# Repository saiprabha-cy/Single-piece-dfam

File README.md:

# Single-Piece DfAM Redesign of a Liquid Rocket Injector/Nozzle Assembly

A capstone project applying **Design for Additive Manufacturing (DfAM)**
principles to a small liquid rocket engine injector/nozzle assembly —
exploring how a traditionally multi-part, bolted engine assembly can be
redesigned as a single consolidated 3D-printed part.

## Motivation

Several modern small-launch-vehicle companies have moved toward 3D-printing
entire rocket engines as a single piece, eliminating the joints, fasteners,
and assembly steps of traditionally machined multi-part engines. This
project applies that same design philosophy at a smaller, student-accessible
scale: take a conventionally-designed multi-part injector/nozzle assembly,
redesign it as one consolidated additively-manufactured part, and validate
the redesign with both hand calculations and simulation.

## Project Stages

| Stage | Folder | Status |
|---|---|---|
| 1. Propulsion calculations | `01_calculations/` | ✅ Complete |
| 2. Baseline multi-part CAD | `02_cad/baseline_multipart/` | ✅ Complete |
| 3. Single-piece DfAM redesign | `02_cad/dfam_redesign/` | ✅ Complete |
| 4. Structural/thermal validation | `03_simulation/` | ✅ Structural complete; thermal documented as a known limitation |
| 5. Sensor/telemetry board | `04_kicad_board/` | ✅ Complete (0 DRC errors) |
| 6. Print-readiness analysis | `05_print_readiness/` | 🔜 Scoped as future work (see below) |
| 7. Final report | `06_report/` | ✅ Complete |

## Design Case (Assumed, Representative Values)

This project uses **representative values** for a generic small LOX/Kerosene
test-case engine, not any specific company's proprietary specifications.

- Target thrust: 3,000 N
- Chamber pressure: 20 bar
- Propellants: LOX / Kerosene (RP-1)
- Assumed sea-level Isp: 290 s

## Key Results

| Metric | Baseline (multi-part) | Redesign (single-piece) |
|---|---|---|
| Part count | 3 | 1 |
| Fastener interfaces | 2 (1 bolted, 1 rigid-joint only) | 0 |
| Mounting holes | 8 | 0 |
| Cooling provisions | None | 6 integrated channels |
| Structural safety factor (20 bar) | — | 6.24 (Ti-6Al-4V, SimScale) |

## Tools Used

- **Python** (SciPy) — propulsion calculations
- **Autodesk Fusion 360** (Personal Use license) — CAD modeling + built-in simulation
- **SimScale** — structural/thermal validation
- **KiCad** — sensor/telemetry PCB design

### Future Extensions
- **PrusaSlicer / Cura** — print-readiness and support-structure analysis
  (scoped as future work; see `05_print_readiness/`)
- Coolant inlet/outlet port routing on the DfAM redesign
- Full channel count (6 → 24) for production-representative coverage
- Chamber L* correction (increase straight-section length for realistic
  combustion residence time)

## Known Limitations

- **Chamber L\*** (characteristic length) is 263mm against a typical
  800-1500mm range for LOX/Kerosene engines — the as-modeled chamber is
  shorter than standard practice would recommend. This is a known,
  documented simplification; it does not affect the validity of the
  single-piece consolidation comparison, which is geometry-independent of
  chamber length. See `01_calculations/results/design_targets.json`.
- **Thermal simulation** was attempted in SimScale but diverged (likely due
  to an incomplete fluid-flow boundary definition in the initial CHT setup).
  Due to free-tier compute limits, a corrected re-run was not completed.
  The Stage 1 hand-calculated estimate (19.2 MW/m², target wall temp 800K)
  is retained as the primary thermal reference. See
  `03_simulation/validation_comparison.md`.
- **Cooling channel count** was reduced from a production-representative
  24 channels to 6, to keep the modeling scope achievable within the
  project timeline.
- **Print-readiness analysis** (slicer-based orientation/support check) was
  not completed; see Future Extensions above.

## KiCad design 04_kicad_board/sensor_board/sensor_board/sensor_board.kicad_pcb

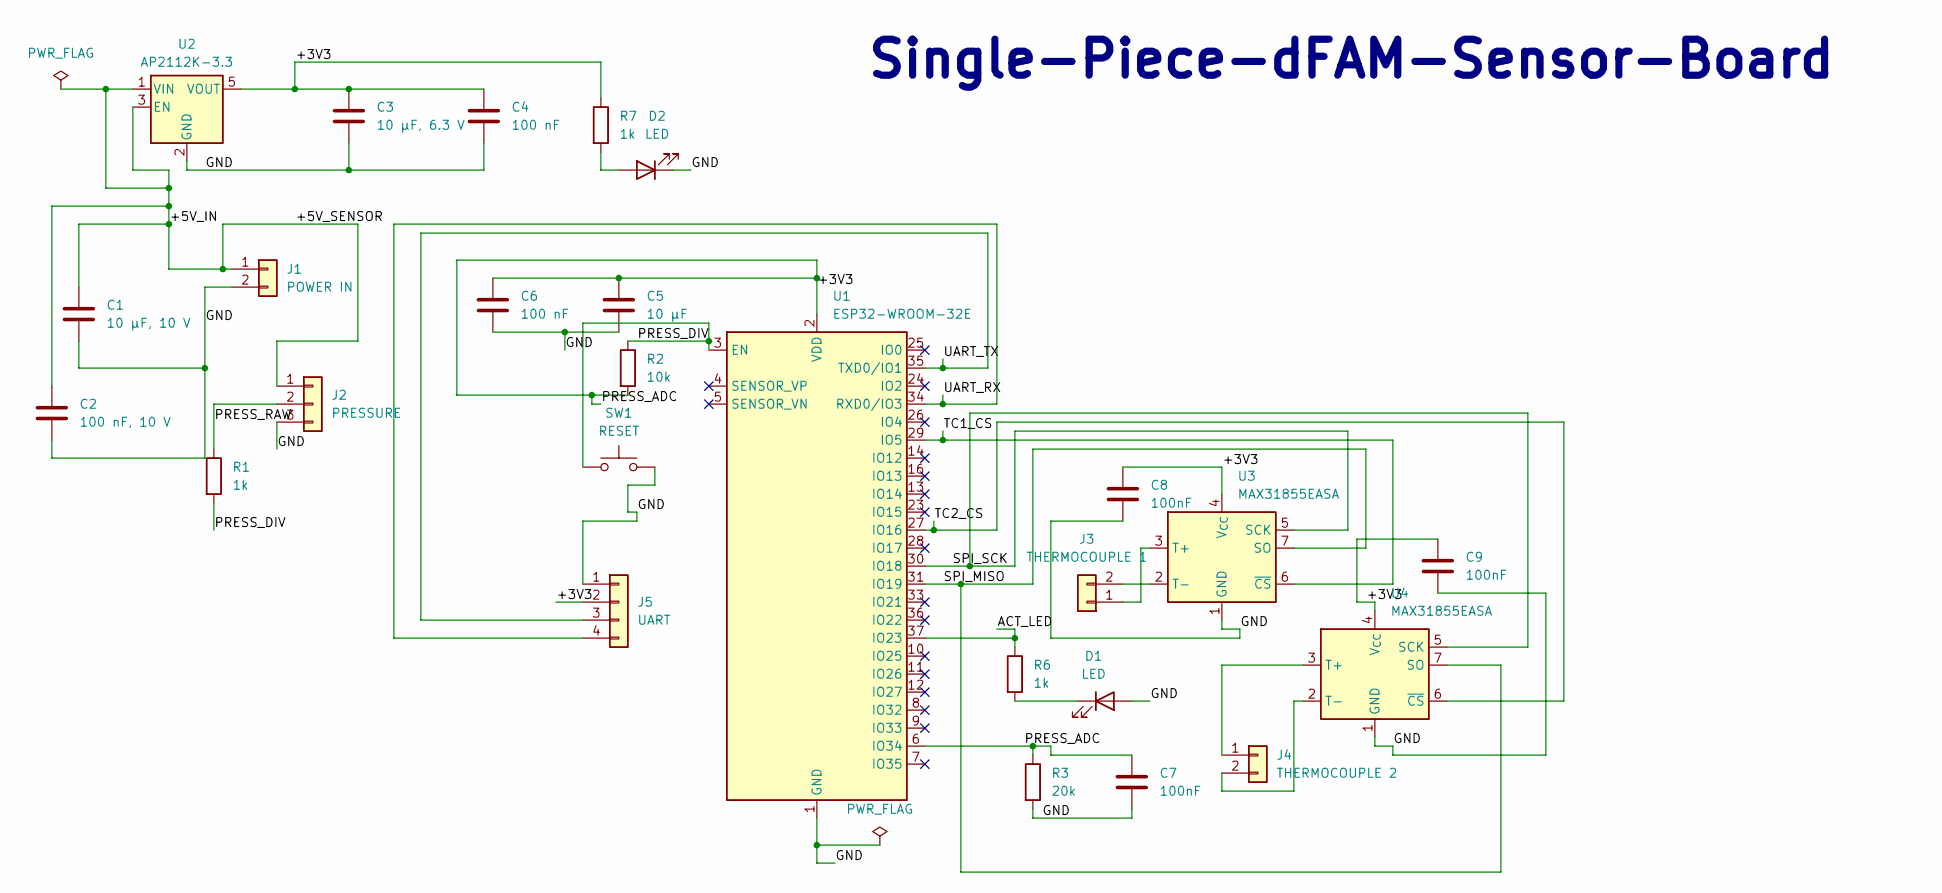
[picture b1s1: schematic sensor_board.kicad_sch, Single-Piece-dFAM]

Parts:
C1: 10 µF, 10 V; C_0805_2012Metric
C2: 100 nF, 10 V; C_0603_1608Metric
C3: 10 µF, 6.3 V; C_0805_2012Metric
C4, C6: 100 nF; C_0603_1608Metric
C5: 10 µF; C_0805_2012Metric
C7, C8, C9: 100nF; C_0603_1608Metric
D1, D2: LED; LED_0603_1608Metric
J1: POWER IN; PhoenixContact_MSTBA_2,5_2-G_1x02_P5.00mm_Horizontal
J2: PRESSURE; PinHeader_1x03_P2.54mm_Vertical
J3: THERMOCOUPLE 1; PinHeader_1x02_P2.54mm_Vertical
J4: THERMOCOUPLE 2; PinHeader_1x02_P2.54mm_Vertical
J5: UART; PinHeader_1x04_P2.54mm_Vertical
R1, R6, R7: 1k; R_0603_1608Metric
R2: 10k; R_0603_1608Metric
R3: 20k; R_0603_1608Metric
SW1: RESET; SW_SPST_TL3305A
U1: ESP32-WROOM-32E; ESP32-WROOM-32
U2: AP2112K-3.3; SOT-23-5
U3, U4: MAX31855EASA; SOIC-8_3.9x4.9mm_P1.27mm

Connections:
/+3V3: C3.1, C4.1, C5.1, C6.1, C7.1, C8.1, C9.1, J5.2, R2.2, R3.1, R7.1, U1.2 (VDD), U1.6 (IO34), U2.5 (VOUT), U3.4 (V_{CC}), U4.4 (V_{CC})
/+5V_IN: C1.1, C2.1, J1.1, J2.1, U2.1 (VIN), U2.3 (EN)
/ACT_LED: R6.1, U1.37 (IO23)
/GND: C1.2, C2.2, C3.2, C4.2, C5.2, C6.2, C7.2, C8.2, C9.2, D1.2 (A), D2.1 (K), J1.2, J2.3, J5.1, R3.2, SW1.2, U1.1 (GND), U1.15 (GND), U1.38 (GND), U1.39 (GND), U2.2 (GND), U3.1 (GND), U4.1 (GND)
/PRESS_DIV: R1.2, R2.1, SW1.1, U1.3 (EN)
/PRESS_RAW: J2.2, R1.1
/SPI_MISO: U1.31 (IO19), U3.7 (SO), U4.7 (SO)
/SPI_SCK: U1.30 (IO18), U3.5 (SCK), U4.5 (SCK)
/TC1_CS: U1.29 (IO5), U3.6 (~CS)
/TC2_CS: U1.27 (IO16), U4.6 (~CS)
/UART_RX: J5.4, U1.34 (RXD0/IO3)
/UART_TX: J5.3, U1.35 (TXD0/IO1)
unnamed: D1.1 (K), R6.2
unnamed: D2.2 (A), R7.2
unnamed: J3.1, U3.3 (T+)
unnamed: J3.2, U3.2 (T-)
unnamed: J4.1, U4.3 (T+)
unnamed: J4.2, U4.2 (T-)

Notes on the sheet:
Single-Piece-dFAM-Sensor-Board

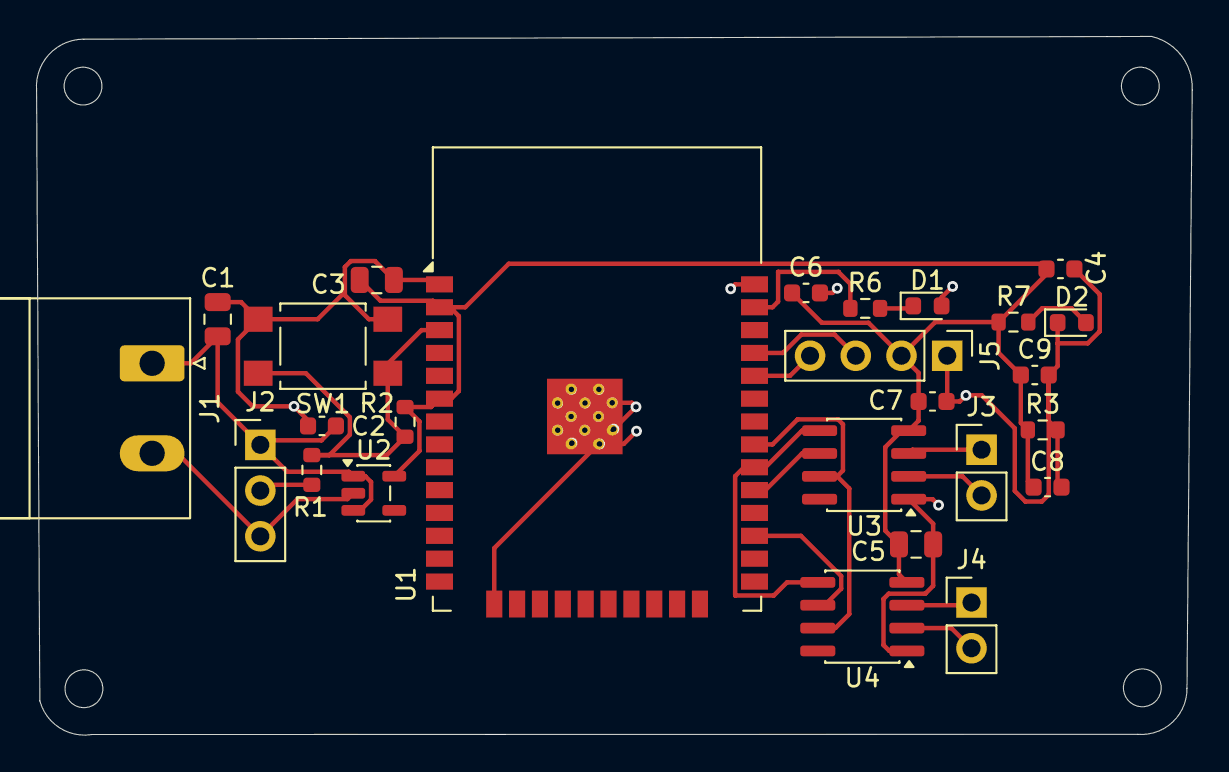
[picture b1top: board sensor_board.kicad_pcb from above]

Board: 2 copper layers, 64.2 x 38.8 mm, 26 parts (0 on the bottom side), 18 nets.
